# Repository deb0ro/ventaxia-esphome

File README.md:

# ventaxia-esphome – ESP32-S3 control board for Vent-Axia Sentinel Kinetic MVHR

A drop-in replacement for the **Vent-Axia 439150 control board** of the older two-board Sentinel Kinetic heat
recovery units (control board 439150 + power board 439155). The new board plugs into **J10 of the power board 439155**
with the original 34-way ribbon cable and is controlled from **Home Assistant** through **ESPHome**.

> **Not for the newer single-board units (497497 / 497498).**
> The power board 439155 carries mains voltage. Connect or disconnect the ribbon cable only with the unit unplugged.
> Work inside the unit only if you are qualified to do so. You use this design at your own risk.

> Vent-Axia and Sentinel Kinetic are trademarks of their owners. This is an independent project, not affiliated with
> or endorsed by Vent-Axia. The PCB itself carries no manufacturer name ("VA MVHR control board rev E").

## Status

| | |
|---|---|
| Hardware | **Rev E**, built and running in the unit since 9 Nov 2026 |
| Firmware | `firmware/ventaxia_reve.yaml` (ESPHome 2026.10, ESP-IDF) |
| Earlier prototype | `firmware/ventaxia_alpha.yaml` – NodeMCU ESP8266 on a breadboard (same control logic) |

The control logic runs **on the ESP**. Home Assistant only changes the mode and the settings and shows the state.
Without Home Assistant or Wi-Fi the unit keeps running with the last settings stored in flash.

## Features

- Two EC fans (ebm-papst, 0–10 V PWM input) with tacho feedback, soft ramp, fan-fault detection and latching
- Modes **Auto / Low / Normal / Boost / Manual**, night mode with its own levels and weekend offset
- Three daily **airing** slots, **boost**, **fireplace** (more supply than extract to light a stove),
  **cooker hood** (extract off, supply as make-up air), **holiday**
- **Summer bypass** with hysteresis, **free cooling**, **frost protection** (bypass or airflow mode), cold-house
  protection, dry-air protection (indoor RH from HA)
- **Filter monitoring**: age, run hours and clog detection from the rpm drift at the same PWM against a learned
  clean-filter reference
- Light-switch input (LS) boost, like the original control board
- Rev E extras: 4× DS18B20 (outdoor, supply, extract, exhaust), SHT4x humidity, SCD41 CO₂, heat recovery efficiency
- Fail-safe fan driver: the fans **stop** in reset, while flashing, with the ESP removed or without 3V3/5V

All settings live in one versioned record in flash, so a firmware update does not reset them.
The full description of every function is in the header of [firmware/ventaxia_reve.yaml](firmware/ventaxia_reve.yaml).

## Repository layout

| Path | Content |
|---|---|
| [hardware/mvhr_ctrl/](hardware/mvhr_ctrl/) | KiCad 10 project of rev E, schematic and assembly PDF, BOM, renders, fab data |
| [hardware/mvhr_ctrl/fab/](hardware/mvhr_ctrl/fab/) | `mvhr_ctrl_jlcpcb.zip` (Gerber X2 + Excellon), ODB++, single Gerber files |
| [hardware/tools/](hardware/tools/) | Python generators of the schematic, board, footprint, fab data and the drawings below |
| [hardware/mvhr_ctrl/README.cs.md](hardware/mvhr_ctrl/README.cs.md) | Detailed hardware notes in Czech (fab rules, fault behaviour, review items) |
| [firmware/](firmware/) | ESPHome configurations and their generator |
| [docs/bring-up.md](docs/bring-up.md) | Step-by-step bring-up and measurements |
| [docs/control_strategy.cs.md](docs/control_strategy.cs.md) | How the unit should be controlled, background for the logic (Czech) |

## Hardware (rev E)

- 95 × 95 mm, 2 layers, 1.6 mm, **through-hole parts only** – assembled at home
- MCU: **ESP32-S3-DevKitC-1** (N8R8 or N16R8) in two 1×22 sockets. The **Waveshare ESP32-S3-DEV-KIT-N8R8** is pin
  compatible; it overhangs the right board edge by about 2 mm
- Power: 24 V from J10 → PTC fuse F1 → TVS P6KE47CA → **TRACO TSR 1-4850WI** (9–72 V in, 5 V) → 1N5819 → DevKit 5V pin
- Fan PWM: two transistor stages per fan (Q3/Q1, Q4/Q2), **non-inverted** (GPIO high = fan runs); Q1/Q2 are biased on
  from the motor's own +10 V, so the PWM line is held low (fan stopped) whenever the ESP does not actively drive it
- Connectors: J1 box header 2×17 to 439155 J10, J4–J7 JST XH-3 (1-Wire), J8/J9 JST XH-4 (I²C)

| Document | |
|---|---|
| Schematic | [mvhr_ctrl_schematic.pdf](hardware/mvhr_ctrl/mvhr_ctrl_schematic.pdf) |
| BOM | [mvhr_ctrl_bom.csv](hardware/mvhr_ctrl/mvhr_ctrl_bom.csv), purchase list incl. DevKit, sockets and cables [nakup_revE.csv](hardware/mvhr_ctrl/nakup_revE.csv) |
| Assembly | [assembly map](hardware/mvhr_ctrl/assembly_map_revE_en.png) (every part with value and polarity; Czech: [osazovaci_mapa_revE.png](hardware/mvhr_ctrl/osazovaci_mapa_revE.png)), [assembly PDF](hardware/mvhr_ctrl/mvhr_ctrl_assembly.pdf) |
| J1 / J10 pinout | [J1_pinout_top_en.png](hardware/mvhr_ctrl/J1_pinout_top_en.png) (Czech: [J1_pinout_top.png](hardware/mvhr_ctrl/J1_pinout_top.png)) |

### Assembly map

Top view with every part's reference, value and polarity, the BOM grouped by value and the recommended soldering
order. Vector version: [assembly_map_revE_en.svg](hardware/mvhr_ctrl/assembly_map_revE_en.svg); Czech version: [osazovaci_mapa_revE.png](hardware/mvhr_ctrl/osazovaci_mapa_revE.png).

### J10 / J1 pinout (34-way ribbon, 1:1)

Top view of J1 as placed on the board (same numbering as J10 on the power board 439155):

| Pin | Signal | Pin | Signal |
|---|---|---|---|
| 1, 2 | +24 V | 5–8, 12, 20, 28, 32 | GND |
| 10 / 14 / 16 | FAN1 (extract) tacho / PWM / +10 V | 18 / 22 / 24 | FAN2 (supply) tacho / PWM / +10 V |
| 13 | LS – light switch input (opto on 439155) | 26 | bypass relay (base of BC337 on 439155) |
| 30 | NTC1 TEMP1 (extract air) | 34 | NTC2 TEMP2 (outdoor) |

### ESP32-S3 pin map

| GPIO | Function | GPIO | Function |
|---|---|---|---|
| 4 | FAN1 extract PWM (ledc, 1 kHz) | 1 | NTC1 TEMP1, ADC1_CH0 |
| 5 | FAN2 supply PWM | 2 | NTC2 TEMP2, ADC1_CH1 |
| 6 | FAN1 tacho (PCNT) | 8 / 9 | I²C SDA / SCL (SHT4x 0x44, SCD41 0x62) |
| 7 | FAN2 tacho (PCNT) | 17 | 1-Wire, 4× DS18B20 |
| 15 | bypass relay | 18 | status LED D3 |
| 16 | LS input | | |

### Notes from the build

- **F1:** designed for Littelfuse RXEF030; **RXEF040 (Littelfuse RF2566)** works as well (same 72 V rating and
  5.1 mm pitch, hold 0.4 A). The board draws about 0.1–0.15 A from 24 V.
- With the Waveshare DevKit, check that 3V3 stays above 3.2 V under Wi-Fi load (its LDO may be an AMS1117).

### Ordering the PCB

Upload `hardware/mvhr_ctrl/fab/mvhr_ctrl_jlcpcb.zip` to JLCPCB: 2 layers, 95 × 95 mm, FR-4, 1.6 mm, 1 oz,
HASL lead-free, no assembly.

### Regenerating the design

The schematic and the board are generated by scripts. Run them with KiCad 10's Python
(`C:\Program Files\KiCad\10.0\bin\python.exe` on Windows) from `hardware/tools`:

```
python make_fp_tsr1wi.py         # TRACO TSR 1WI footprint with case pins
python build_sch_e.py            # schematic
python route_e_until_clean.py    # board placement + Freerouting until DRC is clean
python export_fab_e.py           # Gerber, drill, ODB++, PDFs, BOM, renders
python make_assembly_map.py [en] # assembly map SVG (Czech, or English with "en")
python make_j1_pinout.py [en]    # J1 pinout SVG (Czech, or English with "en")
```

Routing needs Freerouting 2.5.0 and a Java runtime in `hardware/tools/ext/` (`freerouting/freerouting-2.5.0.jar`);
they are not part of the repository. Freerouting is not deterministic, so a rerun gives a different track layout.

## Firmware

1. Copy `firmware/secrets.example.yaml` to `firmware/secrets.yaml` and fill in Wi-Fi, API key and passwords.
2. Flash `firmware/ventaxia_reve.yaml` with ESPHome. The first flash goes over USB, later updates over Wi-Fi.
3. Add the device in Home Assistant (ESPHome integration) with the API encryption key.

The YAML files are **generated** – edit `firmware/gen/fw_template.yaml` (logic shared by both boards) and
`firmware/gen/reve.py` (rev E hardware layer), then run:

```
python firmware/gen/gen_fw.py
```

With a `secrets.yaml` present it also writes `*_builder.yaml` copies with the secrets inlined for the ESPHome Builder
app; those copies are git-ignored and must never be committed.

Before using it in your home, adapt the substitutions at the top of the YAML: the Home Assistant entities used as
backups (`ha_outdoor`, `ha_indoor_rh`, `ha_indoor_t`), the NTC parameters and the DS18B20 addresses (printed in the
log after the first boot with the sensors connected).

## Bring-up

Follow [docs/bring-up.md](docs/bring-up.md): visual check, resistance checks without power, 24 V without the ESP,
with the ESP, and finally in the unit – first without the ESP to confirm that the fans stay stopped.

## License

| Part | License |
|---|---|
| Hardware (`hardware/mvhr_ctrl/`) and documentation (`docs/`) | [CC BY-NC-SA 4.0](LICENSES/CC-BY-NC-SA-4.0.txt) – you may build, modify and share it for non-commercial use with attribution; shared adaptations keep the same licence. Selling boards, kits or the design needs the author's permission |
| Firmware (`firmware/`) and generator scripts (`hardware/tools/`) | [MIT](LICENSES/MIT.txt) |

Details in [LICENSE](LICENSE). Vent-Axia and Sentinel Kinetic are trademarks of their owners and are used only to
describe compatibility.

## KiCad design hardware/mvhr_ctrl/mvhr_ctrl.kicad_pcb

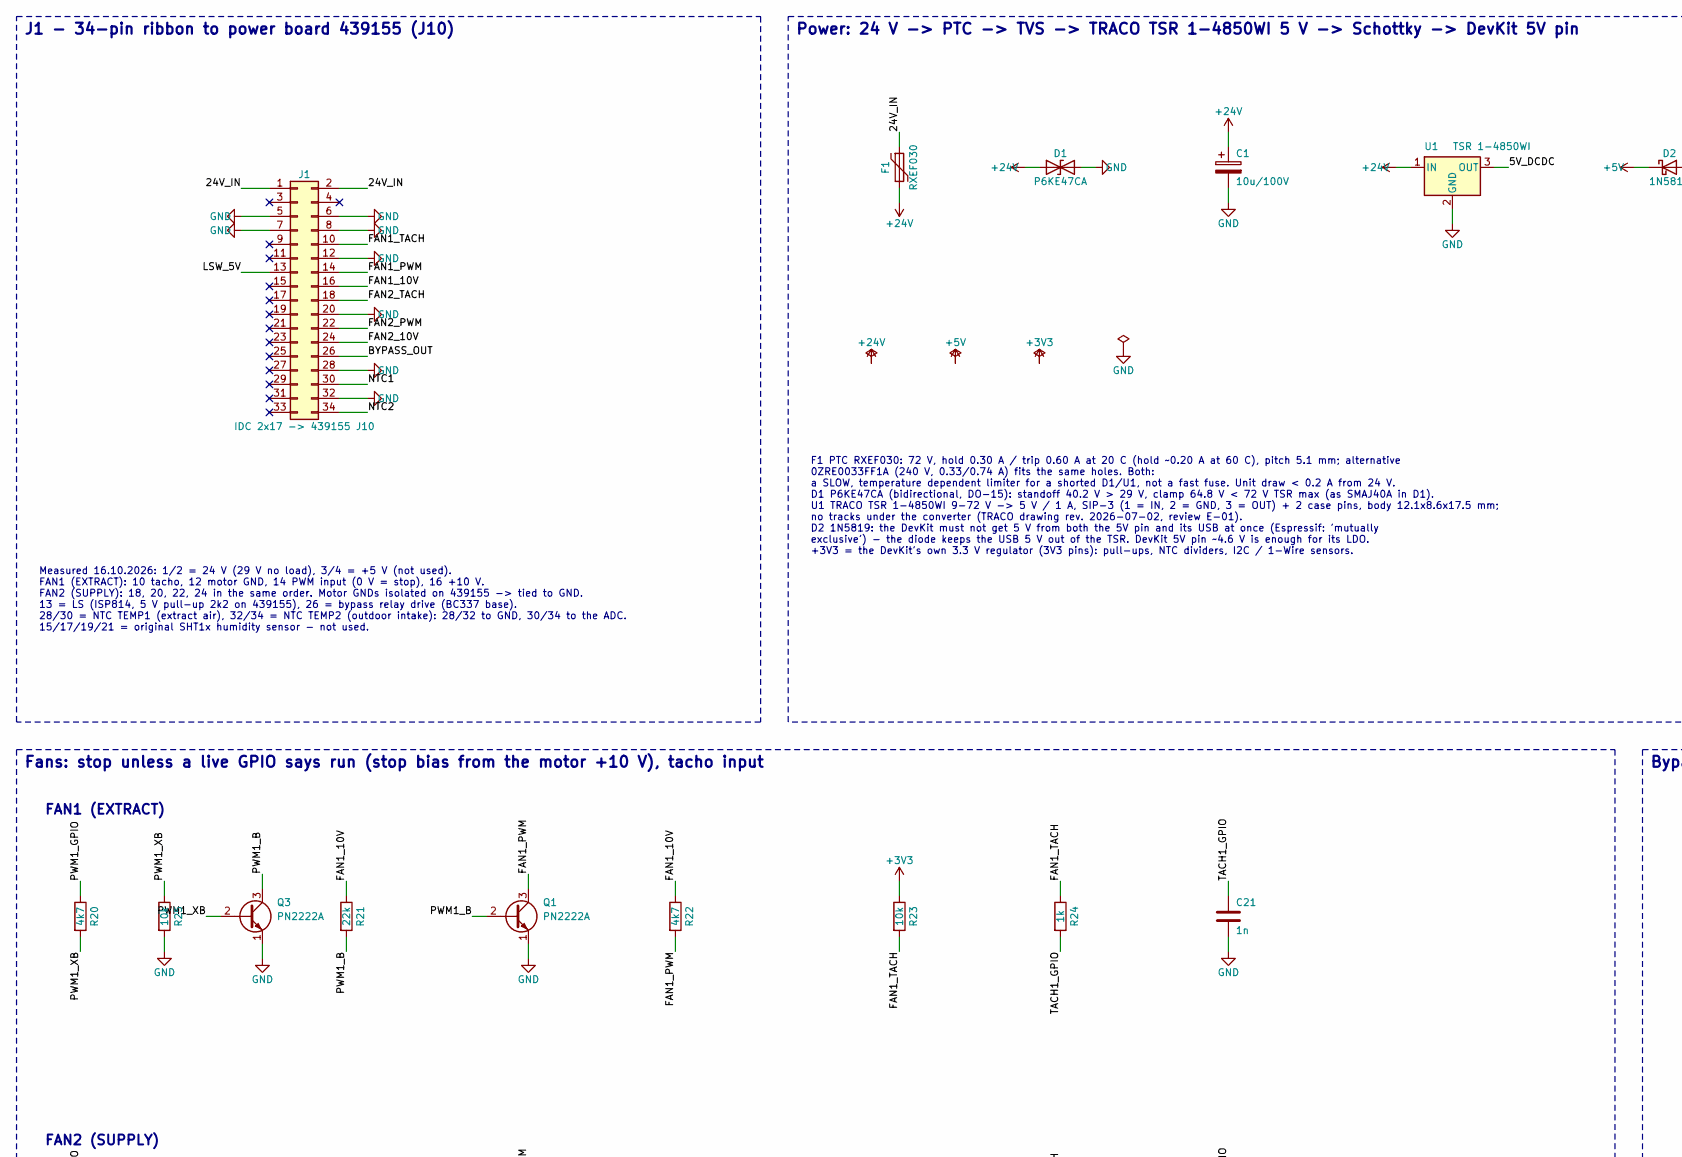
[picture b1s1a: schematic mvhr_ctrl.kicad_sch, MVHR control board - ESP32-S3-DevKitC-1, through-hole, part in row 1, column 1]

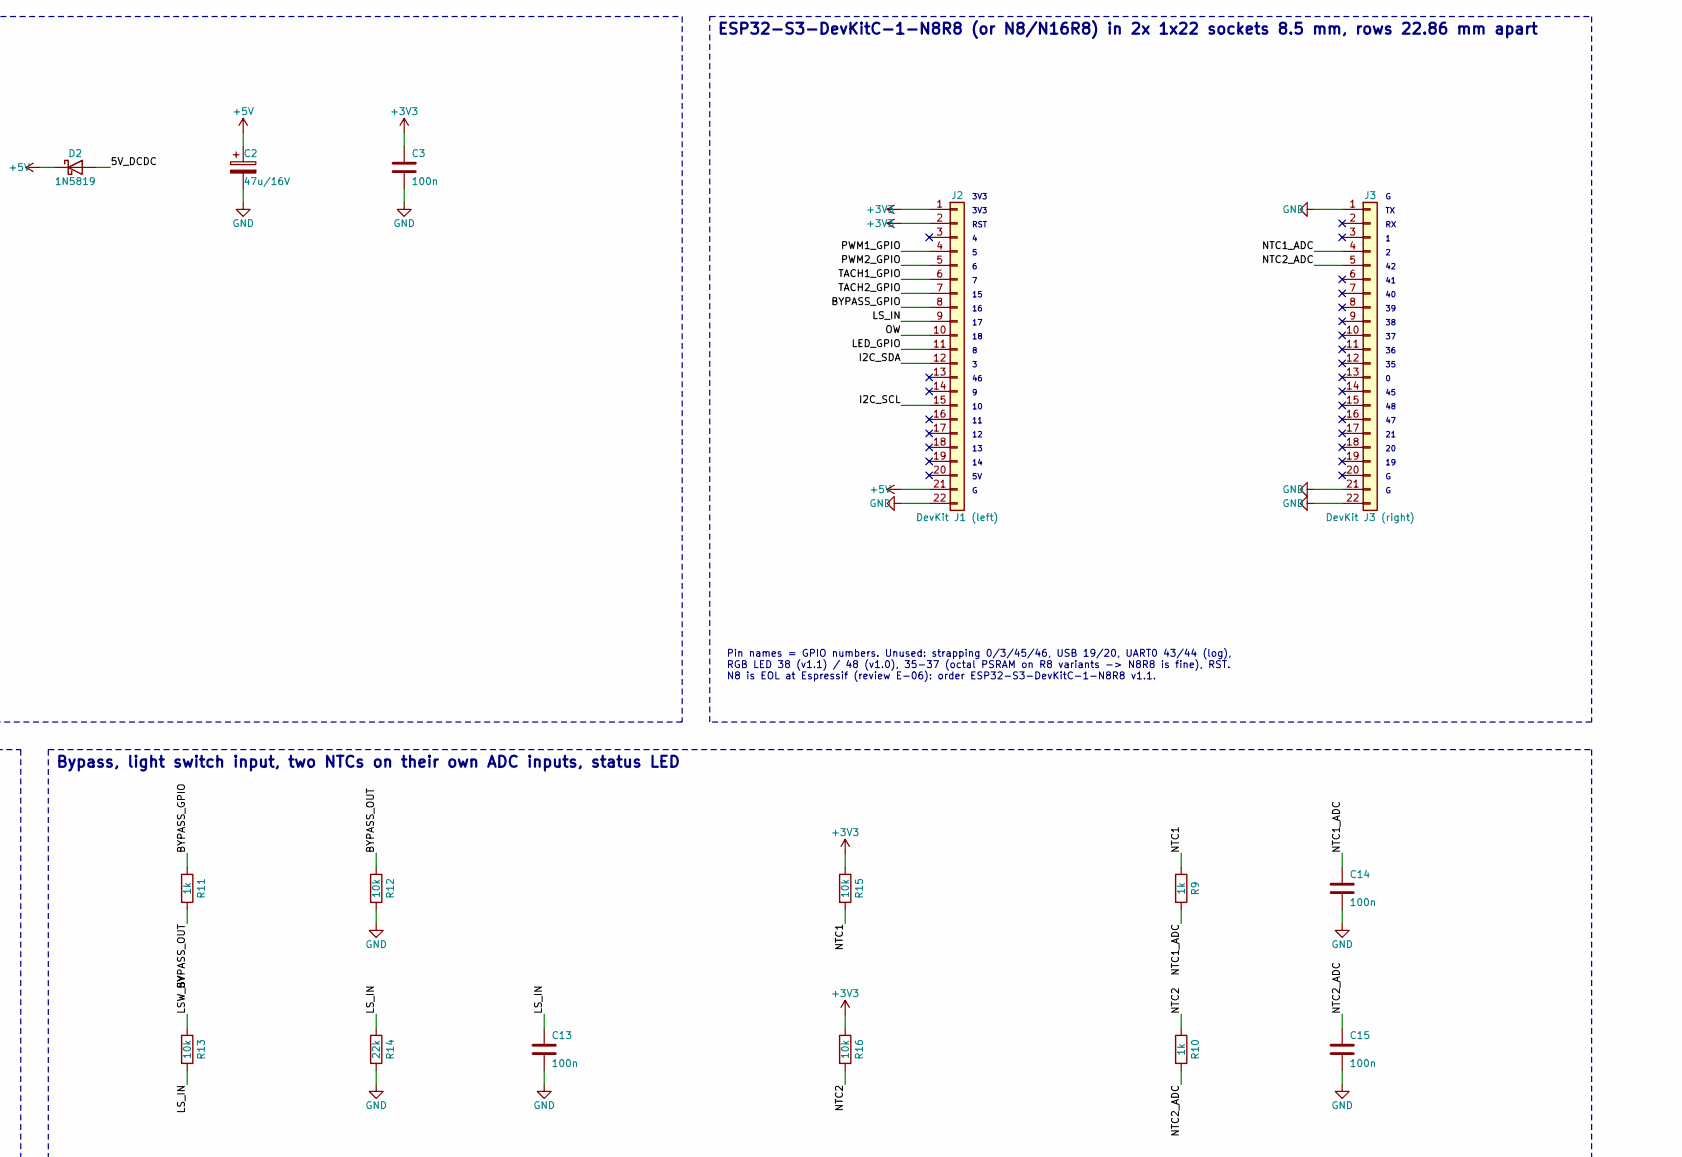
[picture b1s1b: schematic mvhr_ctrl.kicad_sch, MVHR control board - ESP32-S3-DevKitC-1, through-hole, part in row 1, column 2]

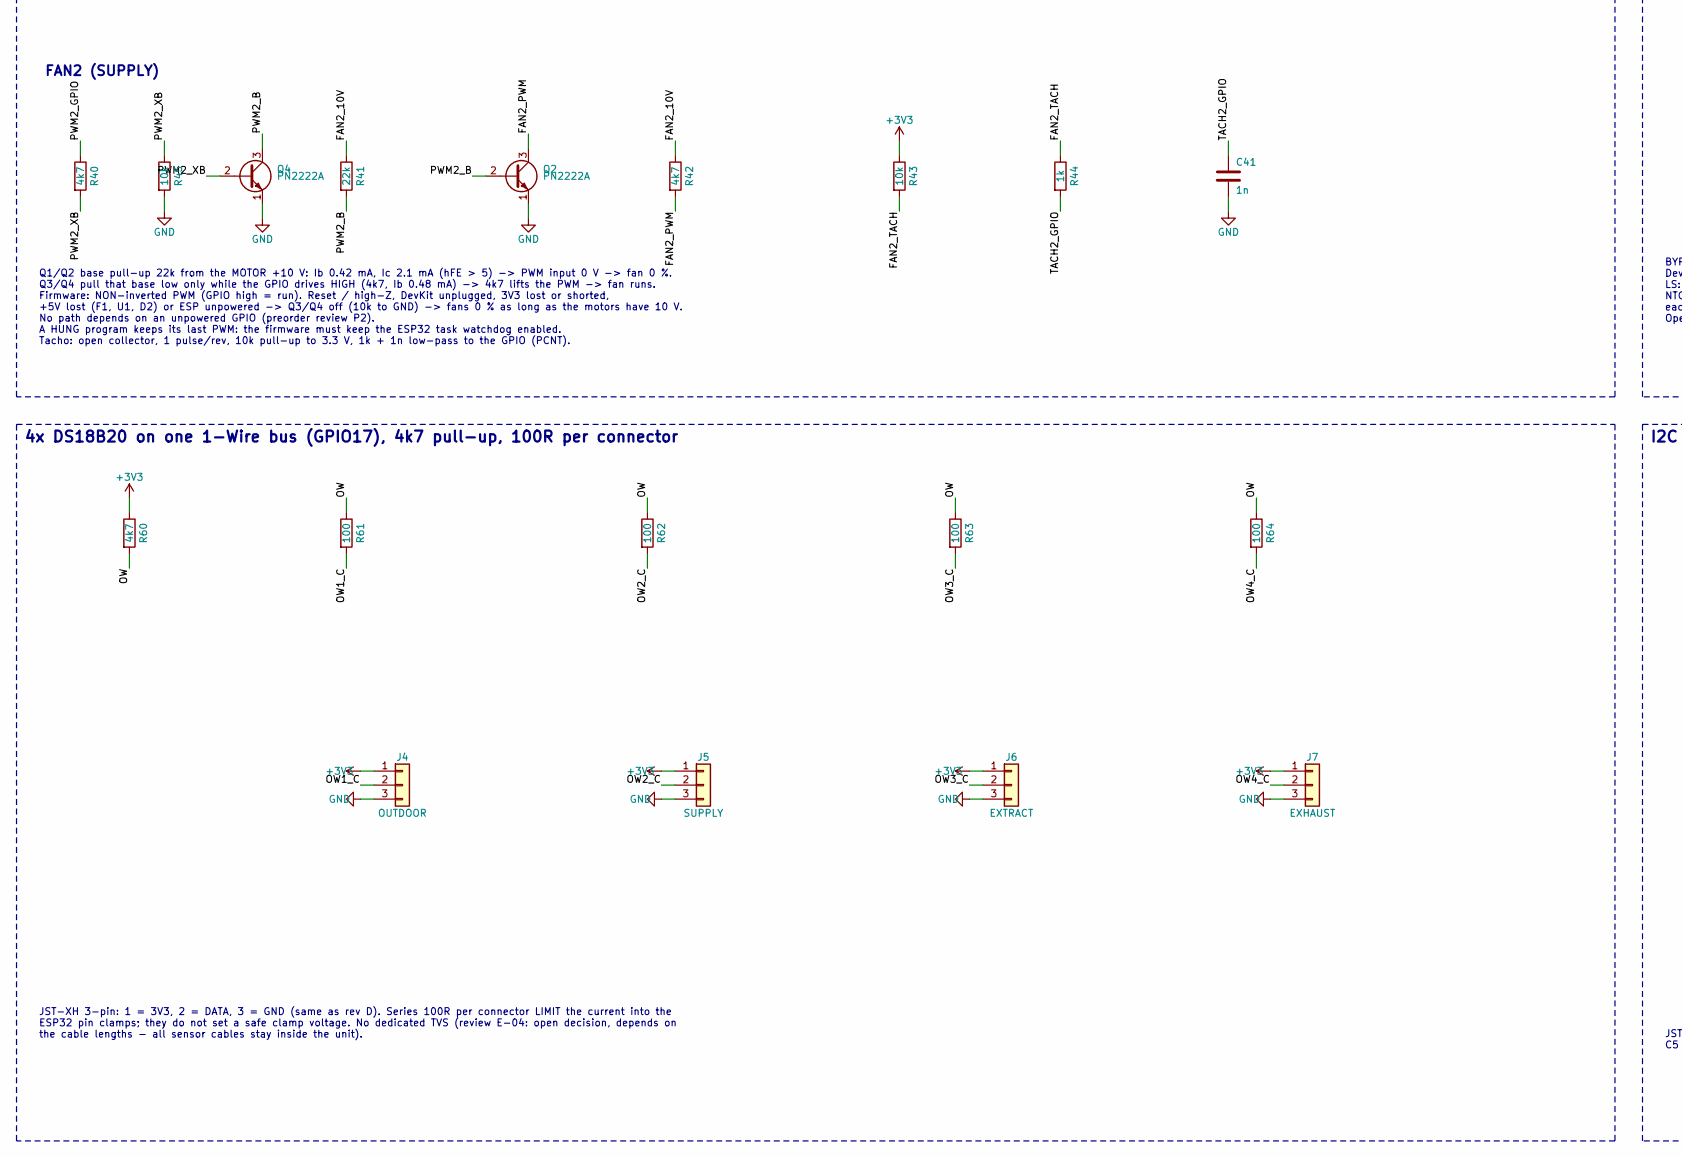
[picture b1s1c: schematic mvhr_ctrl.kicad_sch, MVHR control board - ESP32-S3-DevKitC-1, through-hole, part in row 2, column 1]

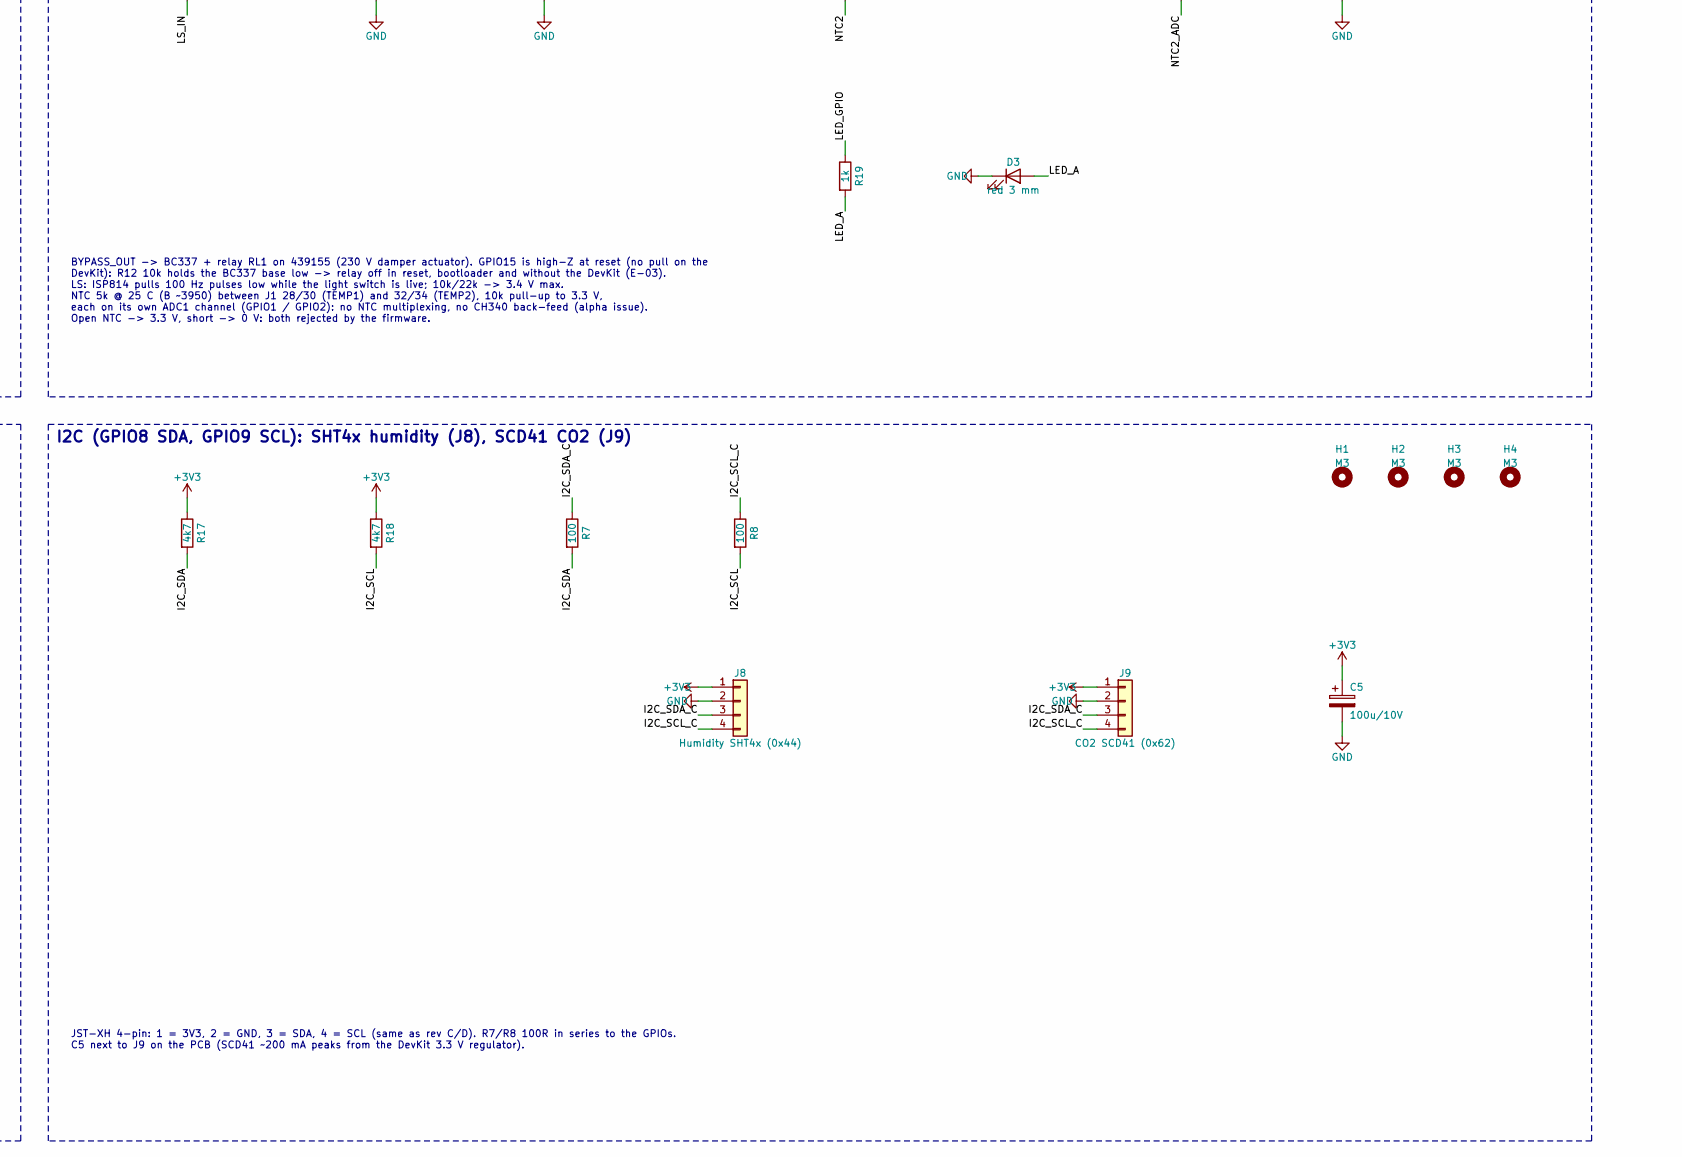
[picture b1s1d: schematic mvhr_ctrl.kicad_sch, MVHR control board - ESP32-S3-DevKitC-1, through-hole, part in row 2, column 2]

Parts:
C1: 10u/100V; CP_Radial_D8.0mm_P3.50mm; MPN Electrolytic 10 uF 100 V, D8 P3.5
C2: 47u/16V; CP_Radial_D6.3mm_P2.50mm
C3, C13, C14, C15: 100n; C_Disc_D5.0mm_W2.5mm_P5.00mm
C5: 100u/10V; CP_Radial_D6.3mm_P2.50mm
C21, C41: 1n; C_Disc_D5.0mm_W2.5mm_P5.00mm
D1: P6KE47CA; D_DO-15_P10.16mm_Horizontal; MPN P6KE47CA (40.2 V standoff, 64.8 V clamp)
D2: 1N5819; D_DO-41_SOD81_P10.16mm_Horizontal
D3: red 3 mm; LED_D3.0mm
F1: RXEF030; Fuse_BelFuse_0ZRE0033FF_L11.4mm_W3.8mm; MPN Littelfuse RXEF030 (72 V, hold 0.30 A /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
H1, H2, H3, H4: M3; MountingHole_3.2mm_M3
J1: IDC 2x17 -> 439155 J10; IDC-Header_2x17_P2.54mm_Vertical; MPN Box header 2x17 2.54mm
J2: DevKit J1 (left); PinSocket_1x22_P2.54mm_Vertical; MPN Female header 1x22 2.54 mm
J3: DevKit J3 (right); PinSocket_1x22_P2.54mm_Vertical; MPN Female header 1x22 2.54 mm
J4: OUTDOOR; JST_XH_B3B-XH-A_1x03_P2.50mm_Vertical; MPN JST B3B-XH-A
J5: SUPPLY; JST_XH_B3B-XH-A_1x03_P2.50mm_Vertical; MPN JST B3B-XH-A
J6: EXTRACT; JST_XH_B3B-XH-A_1x03_P2.50mm_Vertical; MPN JST B3B-XH-A
J7: EXHAUST; JST_XH_B3B-XH-A_1x03_P2.50mm_Vertical; MPN JST B3B-XH-A
J8: Humidity SHT4x (0x44); JST_XH_B4B-XH-A_1x04_P2.50mm_Vertical; MPN JST B4B-XH-A
J9: CO2 SCD41 (0x62); JST_XH_B4B-XH-A_1x04_P2.50mm_Vertical; MPN JST B4B-XH-A
Q1, Q2, Q3, Q4: PN2222A; TO-92_Inline_Wide; MPN onsemi PN2222A (TO-92, pins E-B-C = 1-2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
R7, R8, R61, R62, R63, R64: 100; R_Axial_DIN0207_L6.3mm_D2.5mm_P7.62mm_Horizontal
R9, R10, R11, R19, R24, R44: 1k; R_Axial_DIN0207_L6.3mm_D2.5mm_P7.62mm_Horizontal
R12, R13, R15, R16, R23, R25, R43, R45: 10k; R_Axial_DIN0207_L6.3mm_D2.5mm_P7.62mm_Horizontal
R14, R21, R41: 22k; R_Axial_DIN0207_L6.3mm_D2.5mm_P7.62mm_Horizontal
R17, R18, R20, R22, R40, R42, R60: 4k7; R_Axial_DIN0207_L6.3mm_D2.5mm_P7.62mm_Horizontal
U1: TSR 1-4850WI; TRACO_TSR-1WI_SIP3_CasePins; MPN TRACO TSR 1-4850WI, straight pins (9-72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

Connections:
+3V3: C3.1, C5.1, J2.1, J2.2, J4.1, J5.1, J6.1, J7.1, J8.1, J9.1, R15.1, R16.1, R17.1, R18.1, R23.1, R43.1, R60.1
+5V: C2.1, D2.1 (K), J2.21
+24V: C1.1, D1.1 (A1), F1.2, U1.1 (IN)
/5V_DCDC: D2.2 (A), U1.3 (OUT)
/24V_IN: F1.1, J1.1, J1.2
/BYPASS_GPIO: J2.8, R11.1
/BYPASS_OUT: J1.26, R11.2, R12.1
/FAN1_10V: J1.16, R21.1, R22.1
/FAN1_PWM: J1.14, Q1.3 (C), R22.2
/FAN1_TACH: J1.10, R23.2, R24.1
/FAN2_10V: J1.24, R41.1, R42.1
/FAN2_PWM: J1.22, Q2.3 (C), R42.2
/FAN2_TACH: J1.18, R43.2, R44.1
/I2C_SCL: J2.15, R8.2, R18.2
/I2C_SCL_C: J8.4, J9.4, R8.1
/I2C_SDA: J2.12, R7.2, R17.2
/I2C_SDA_C: J8.3, J9.3, R7.1
/LED_A: D3.2 (A), R19.2
/LED_GPIO: J2.11, R19.1
/LSW_5V: J1.13, R13.1
/LS_IN: C13.1, J2.9, R13.2, R14.1
/NTC1: J1.30, R9.1, R15.2
/NTC1_ADC: C14.1, J3.4, R9.2
/NTC2: J1.34, R10.1, R16.2
/NTC2_ADC: C15.1, J3.5, R10.2
/OW: J2.10, R60.2, R61.1, R62.1, R63.1, R64.1
/OW1_C: J4.2, R61.2
/OW2_C: J5.2, R62.2
/OW3_C: J6.2, R63.2
/OW4_C: J7.2, R64.2
/PWM1_B: Q1.2 (B), Q3.3 (C), R21.2
/PWM1_GPIO: J2.4, R20.1
/PWM1_XB: Q3.2 (B), R20.2, R25.1
/PWM2_B: Q2.2 (B), Q4.3 (C), R41.2
/PWM2_GPIO: J2.5, R40.1
/PWM2_XB: Q4.2 (B), R40.2, R45.1
/TACH1_GPIO: C21.1, J2.6, R24.2
/TACH2_GPIO: C41.1, J2.7, R44.2
GND: C1.2, C2.2, C3.2, C5.2, C13.2, C14.2, C15.2, C21.2, C41.2, D1.2 (A2), D3.1 (K), J1.5, J1.6, J1.7, J1.8, J1.12, J1.20, J1.28, J1.32, J2.22, J3.1, J3.21, J3.22, J4.3, J5.3, J6.3, J7.3, J8.2, J9.2, Q1.1 (E), Q2.1 (E), Q3.1 (E), Q4.1 (E), R12.2, R14.2, R25.2, R45.2, U1.2 (GND)

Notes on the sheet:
J1 - 34-pin ribbon to power board 439155 (J10)
Measured 16.10.2026: 1/2 = 24 V (29 V no load), 3/4 = +5 V (not used). FAN1 (EXTRACT): 10 tacho, 12 motor GND, 14 PWM input (0 V = stop), 16 +10 V. FAN2 (SUPPLY): 18, 20, 22, 24 in the same order. Motor GNDs isolated on 439155 -> tied to GND. 13 = LS (ISP814, 5 V pull-up 2k2 on 439155), 26 = bypass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
Power: 24 V -> PTC -> TVS -> TRACO TSR 1-4850WI 5 V -> Schottky -> DevKit 5V pin
F1 PTC RXEF030: 72 V, hold 0.30 A / trip 0.60 A at 20 C (hold ~0.20 A at 60 C), pitch 5.1 mm; alternative 0ZRE0033FF1A (240 V, 0.33/0.74 A) fits the same holes. Both: a SLOW, temperature dependent limiter for a shorted D1/U1, not a fast fuse. Unit draw < 0.2 A from 24 V. D1 P6KE47CA (bidirectional,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
ESP32-S3-DevKitC-1-N8R8 (or N8/N16R8) in 2x 1x22 sockets 8.5 mm, rows 22.86 mm apart
3V3
RST
Pin names = GPIO numbers. Unused: strapping 0/3/45/46, USB 19/20, UART0 43/44 (log), RGB LED 38 (v1.1) / 48 (v1.0), 35-37 (octal PSRAM on R8 variants -> N8R8 is fine), RST. N8 is EOL at Espressif (review E-06): order ESP32-S3-DevKitC-1-N8R8 v1.1.
Fans: stop unless a live GPIO says run (stop bias from the motor +10 V), tacho input
FAN1 (EXTRACT)
FAN2 (SUPPLY)
Q1/Q2 base pull-up 22k from the MOTOR +10 V: Ib 0.42 mA, Ic 2.1 mA (hFE > 5) -> PWM input 0 V -> fan 0 %. Q3/Q4 pull that base low only while the GPIO drives HIGH (4k7, Ib 0.48 mA) -> 4k7 lifts the PWM -> fan runs. Firmware: NON-inverted PWM (GPIO high = run). Reset / high-Z, DevKit unplugged, 3V3 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
Bypass, light switch input, two NTCs on their own ADC inputs, status LED
BYPASS_OUT -> BC337 + relay RL1 on 439155 (230 V damper actuator). GPIO15 is high-Z at reset (no pull on the DevKit): R12 10k holds the BC337 base low -> relay off in reset, bootloader and without the DevKit (E-03). LS: ISP814 pulls 100 Hz pulses low while the light switch is live; 10k/22k -> 3.4 V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
4x DS18B20 on one 1-Wire bus (GPIO17), 4k7 pull-up, 100R per connector
JST-XH 3-pin: 1 = 3V3, 2 = DATA, 3 = GND (same as rev D). Series 100R per connector LIMIT the current into the ESP32 pin clamps; they do not set a safe clamp voltage. No dedicated TVS (review E-04: open decision, depends on the cable lengths - all sensor cables stay inside the unit).
I2C (GPIO8 SDA, GPIO9 SCL): SHT4x humidity (J8), SCD41 CO2 (J9)
JST-XH 4-pin: 1 = 3V3, 2 = GND, 3 = SDA, 4 = SCL (same as rev C/D). R7/R8 100R in series to the GPIOs. C5 next to J9 on the PCB (SCD41 ~200 mA peaks from the DevKit 3.3 V regulator).

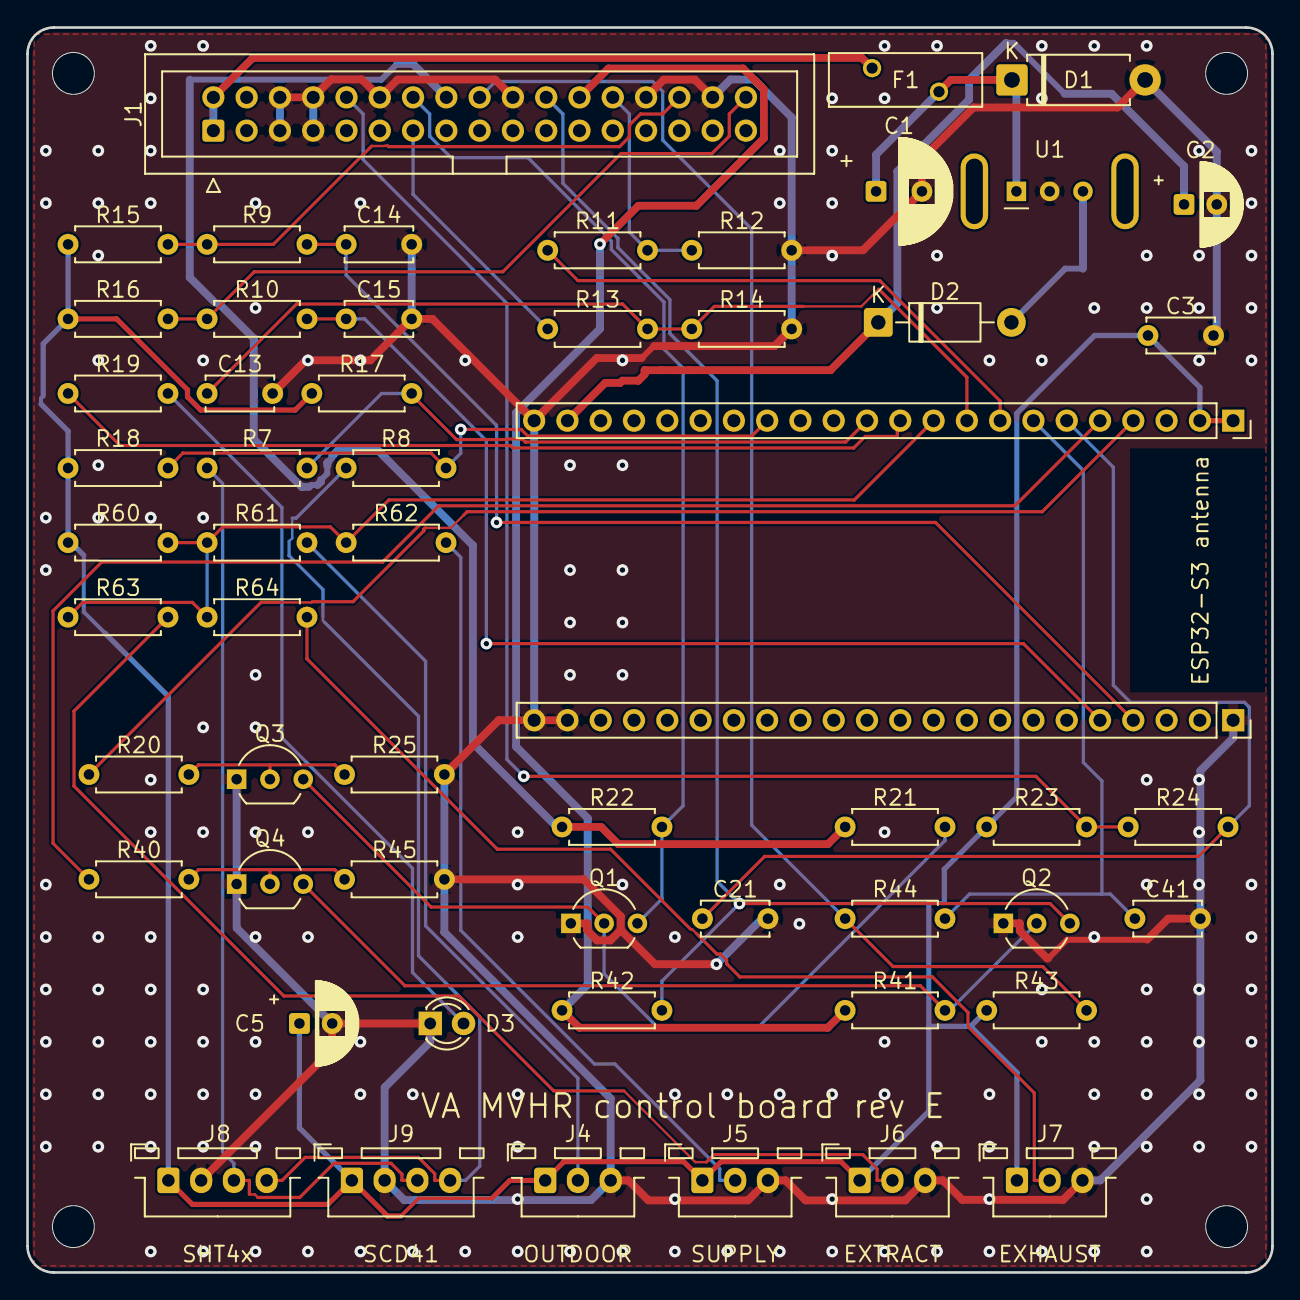
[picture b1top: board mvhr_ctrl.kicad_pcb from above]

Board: 2 copper layers, 95.0 x 95.0 mm, 61 parts (0 on the bottom side), 39 nets.

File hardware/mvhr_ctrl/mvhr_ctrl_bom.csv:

"Reference","Value","Footprint","MPN","Qty"
"C1","10u/100V","Capacitor_THT:CP_Radial_D8.0mm_P3.50mm","Electrolytic 10 uF 100 V, D8 P3.5","1"
"C2","47u/16V","Capacitor_THT:CP_Radial_D6.3mm_P2.50mm","","1"
"C3,C13-C15","100n","Capacitor_THT:C_Disc_D5.0mm_W2.5mm_P5.00mm","","4"
"C5","100u/10V","Capacitor_THT:CP_Radial_D6.3mm_P2.50mm","","1"
"C21,C41","1n","Capacitor_THT:C_Disc_D5.0mm_W2.5mm_P5.00mm","","2"
"D1","P6KE47CA","Diode_THT:D_DO-15_P10.16mm_Horizontal","P6KE47CA (40.2 V standoff, 64.8 V clamp)","1"
"D2","1N5819","Diode_THT:D_DO-41_SOD81_P10.16mm_Horizontal","","1"
"D3","red 3 mm","LED_THT:LED_D3.0mm","","1"
"F1","RXEF030","Fuse:Fuse_BelFuse_0ZRE0033FF_L11.4mm_W3.8mm","Littelfuse RXEF030 (72 V, hold 0.30 A / trip 0.60 A @ 20 C), alt. Bel Fuse 0ZRE0033FF1A","1"
"J1","IDC 2x17 -> 439155 J10","Connector_IDC:IDC-Header_2x17_P2.54mm_Vertical","Box header 2x17 2.54mm","1"
"J2","DevKit J1 (left)","Connector_PinSocket_2.54mm:PinSocket_1x22_P2.54mm_Vertical","Female header 1x22 2.54 mm","1"
"J3","DevKit J3 (right)","Connector_PinSocket_2.54mm:PinSocket_1x22_P2.54mm_Vertical","Female header 1x22 2.54 mm","1"
"J4","OUTDOOR","Connector_JST:JST_XH_B3B-XH-A_1x03_P2.50mm_Vertical","JST B3B-XH-A","1"
"J5","SUPPLY","Connector_JST:JST_XH_B3B-XH-A_1x03_P2.50mm_Vertical","JST B3B-XH-A","1"
"J6","EXTRACT","Connector_JST:JST_XH_B3B-XH-A_1x03_P2.50mm_Vertical","JST B3B-XH-A","1"
"J7","EXHAUST","Connector_JST:JST_XH_B3B-XH-A_1x03_P2.50mm_Vertical","JST B3B-XH-A","1"
"J8","Humidity SHT4x (0x44)","Connector_JST:JST_XH_B4B-XH-A_1x04_P2.50mm_Vertical","JST B4B-XH-A","1"
"J9","CO2 SCD41 (0x62)","Connector_JST:JST_XH_B4B-XH-A_1x04_P2.50mm_Vertical","JST B4B-XH-A","1"
"Q1-Q4","PN2222A","Package_TO_SOT_THT:TO-92_Inline_Wide","onsemi PN2222A (TO-92, pins E-B-C = 1-2-3, flat side as on the silkscreen)","4"
"R7,R8,R61-R64","100","Resistor_THT:R_Axial_DIN0207_L6.3mm_D2.5mm_P7.62mm_Horizontal","","6"
"R9-R11,R19,R24,R44","1k","Resistor_THT:R_Axial_DIN0207_L6.3mm_D2.5mm_P7.62mm_Horizontal","","6"
"R12,R13,R15,R16,R23,R25,R43,R45","10k","Resistor_THT:R_Axial_DIN0207_L6.3mm_D2.5mm_P7.62mm_Horizontal","","8"
"R14,R21,R41","22k","Resistor_THT:R_Axial_DIN0207_L6.3mm_D2.5mm_P7.62mm_Horizontal","","3"
"R17,R18,R20,R22,R40,R42,R60","4k7","Resistor_THT:R_Axial_DIN0207_L6.3mm_D2.5mm_P7.62mm_Horizontal","","7"
"U1","TSR 1-4850WI","mvhr_ctrl:TRACO_TSR-1WI_SIP3_CasePins","TRACO TSR 1-4850WI, straight pins (9-72 V in, 5 V 1 A); case pins 4/5 = mechanical, no net","1"

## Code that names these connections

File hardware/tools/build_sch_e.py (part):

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no SMD part at all (the DevKit brings the 3.3 V regulator, USB and the ESD of its own pins).
DevKit pin map (ESP32-S3-DevKitC-1 v1.0/1.1, header J1 = left, J3 = right):
  GPIO4/5 PWM1/2, GPIO6/7 TACH1/2 (PCNT), GPIO15 bypass, GPIO16 LS, GPIO17 1-Wire, GPIO18 LED,
  GPIO8/9 I2C SDA/SCL, GPIO1/2 NTC1/2 (ADC1_CH0/CH1). Strapping pins 0/3/45/46, USB 19/20, UART 43/44,
  RGB 38/48 and the PSRAM pins 35-37 are left unused.
No manufacturer name on the board (copyright / trademark): the silkscreen says "VA MVHR control board"."""
import os
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
# =====================================================================  DevKit sockets
sch.box(425, 12, 585, 140, "ESP32-S3-DevKitC-1-N8R8 (or N8/N16R8) in 2x 1x22 sockets 8.5 mm, rows 22.86 mm apart")
KJ1 = {1: "+3V3", 2: "+3V3", 4: "PWM1_GPIO", 5: "PWM2_GPIO", 6: "TACH1_GPIO", 7: "TACH2_GPIO",
       8: "BYPASS_GPIO", 9: "LS_IN", 10: "OW", 11: "LED_GPIO", 12: "I2C_SDA", 15: "I2C_SCL", 21: "+5V", 22: "GND"}
KJ1_NAME = ["3V3", "3V3", "RST", "4", "5", "6", "7", "15", "16", "17", "18", "8", "3", "46", "9", "10",
            "11", "12", "13", "14", "5V", "G"]
KJ3 = {1: "GND", 4: "NTC1_ADC", 5: "NTC2_ADC", 21: "GND", 22: "GND"}
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
# =====================================================================  Bypass, LS, NTC, LED
sch.box(305, 145, 585, 275, "Bypass, light switch input, two NTCs on their own ADC inputs, status LED")
R("R11", "1k", 330, 170, "BYPASS_GPIO", "BYPASS_OUT")
R("R12", "10k", 365, 170, "BYPASS_OUT", "GND")          # review E-03: relay OFF while the GPIO floats / no DevKit
R("R13", "10k", 330, 200, "LSW_5V", "LS_IN")
R("R14", "22k", 365, 200, "LS_IN", "GND")
C("C13", "100n", 395, 200, "LS_IN", "GND")
R("R15", "10k", 450, 170, "+3V3", "NTC1")
R("R9", "1k", 510, 170, "NTC1", "NTC1_ADC")              # review E-04: series R between the cable and the ADC pin
C("C14", "100n", 540, 170, "NTC1_ADC", "GND")
R("R16", "10k", 450, 200, "+3V3", "NTC2")
R("R10", "1k", 510, 200, "NTC2", "NTC2_ADC")
C("C15", "100n", 540, 200, "NTC2_ADC", "GND")
R("R19", "1k", 450, 235, "LED_GPIO", "LED_A")
P("D3", "Device:LED", "red 3 mm", 480, 235, {"1": "GND", "2": "LED_A"}, footprint="LED_THT:LED_D3.0mm")
T("BYPASS_OUT -> BC337 + relay RL1 on 439155 (230 V damper actuator). GPIO15 is high-Z at reset (no pull on the\n"
  "DevKit): R12 10k holds the BC337 base low -> relay off in reset, bootloader and without the DevKit (E-03).\n"
  "LS: ISP814 pulls 100 Hz pulses low while the light switch is live; 10k/22k -> 3.4 V max.\n"
  "NTC 5k @ 25 C (B ~3950) between J1 28/30 (TEMP1) and 32/34 (TEMP2), 10k pull-up to 3.3 V,\n"
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sch.box(305, 280, 585, 410, "I2C (GPIO8 SDA, GPIO9 SCL): SHT4x humidity (J8), SCD41 CO2 (J9)")
R("R17", "4k7", 330, 300, "+3V3", "I2C_SDA")
R("R18", "4k7", 365, 300, "+3V3", "I2C_SCL")
R("R7", "100", 400, 300, "I2C_SDA_C", "I2C_SDA")        # review E-04: series R between the cables and the GPIOs
R("R8", "100", 430, 300, "I2C_SCL_C", "I2C_SCL")
SENS = {"1": "+3V3", "2": "GND", "3": "I2C_SDA_C", "4": "I2C_SCL_C"}
P("J8", "Connector_Generic:Conn_01x04", "Humidity SHT4x (0x44)", 430, 330, SENS, footprint=XH4,
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
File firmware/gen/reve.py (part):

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#   GPIO7   FAN2 tacho  <- J10 pin 18
#   GPIO15  bypass      -> R11 1k -> J10 pin 26 (BC337 + relay RL1 on 439155), R12 10k pull-down = off in reset
#   GPIO16  LS input    <- J10 pin 13 (ISP814 on 439155: 100 Hz low pulses while the light switch is live)
#   GPIO1   NTC1 TEMP1 (extract air)  ADC1_CH0, 10k pull-up to 3V3, NTC to GND, 1k + 100n
#   GPIO2   NTC2 TEMP2 (outdoor)      ADC1_CH1
#   GPIO17  1-Wire: 4x DS18B20 (J4 OUTDOOR, J5 SUPPLY, J6 EXTRACT, J7 EXHAUST), 4k7 pull-up
#   GPIO8/9 I2C SDA/SCL: SHT4x 0x44 (J8), SCD41 0x62 (J9), 4k7 pull-ups, 100R in series
#   GPIO18  LED D3 (status_led: off = OK, blinking = warning / error)
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    type: esp-idf
''', 1),
    ('''logger:
  baud_rate: 0                  # UART off: TX (GPIO1) drives NTC2
''', '''logger:                         # USB / UART log free on rev E (no pin shared with the NTCs)
''', 1),
    ('  use_address: 192.168.10.201   # the ESPHome Builder does not find the board via mDNS; keep a DHCP reservation\n',
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          }
          if (!out_ok && api_ok''', 1),
    ('''          const bool boost = id(boost_end) != 0 && (int32_t) (id(boost_end) - now) > 0;''',
     '''          const bool ls = id(ls_boost).state && id(ls_in).state;          // light switch held on
          const bool boost = ls || (id(boost_end) != 0 && (int32_t) (id(boost_end) - now) > 0);''', 1),
    ('''why = boost ? "Boost (timer)" : "Boost"; }''',
     '''why = ls ? "Boost (light switch)" : boost ? "Boost (timer)" : "Boost"; }''', 1),
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      - lambda: |-
          const float vs = 3.3f, rp = 10000.0f;
          auto res = [vs, rp](float v) { return (std::isfinite(v) && v > 0.02f && v < vs - 0.05f) ? rp * v / (vs - v) : NAN; };
          const float r1 = res(id(ntc1_adc).state), r2 = res(id(ntc2_adc).state);
          const bool g1 = std::isfinite(r1) && r1 > 500.0f && r1 < 150000.0f;
          const bool g2 = std::isfinite(r2) && r2 > 500.0f && r2 < 150000.0f;
          if (g1) id(t1_ok_ms) = millis();
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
